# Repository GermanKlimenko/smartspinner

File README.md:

# Умный спиннер для трейдера

Проект **Смартлаба**. Выбранные визуальные направления: [«Пульс рынка»](public/assets/smartlab/market-full.png) и [«Биржевой сигнал»](public/assets/smartlab/signals-full.png). [Галерея на сайте](https://germanklimenko.github.io/smartspinner/#smartlab).

Это концептуальные изображения с демонстрационными котировками, не фотографии работающего прототипа. Свечной вариант не выбран и на сайте не размещён.

[Сайт проекта](https://germanklimenko.github.io/smartspinner/) · [Фото реального POV-вентилятора](public/assets/reference-fan/README.md)

## Текущий этап: неподвижный стенд B0.1

Документация для опытной ручной сборки подготовлена. **На железе не проверено.**
Цель конечного устройства: четыре луча, Ø100 мм, по 20 верхних и 12 торцевых RGB. Это целевые параметры, не характеристики испытанного образца.

- [Полный пакет стенда ZIP](bench/SmartSpinner_B01_DIY_Package.zip)
- [Инструкция PDF](bench/v0.1/output/pdf/SmartSpinner_B01_Bench.pdf)
- [Список покупок](bench/v0.1/shopping.md)
- [Исходники, схема соединений и прошивка](bench/v0.1/)
- [Результаты программных проверок](bench/v0.1/build/verification.txt)
- [Аудит электроники от 29.09.2026](audits/2026-09-29-electronics/README.md)

B0.1: UNO R3, 6 драйверов SM16306SJ, 32 выводных RGB LED, 96 каналов. Неподвижный опыт без аккумулятора и мотора. Не закреплять стенд на купленном голографическом вентиляторе.

## Старые версии сняты

**STOP FABRICATION. Прежние электрические файлы v0.4/v0.5 нельзя использовать для изготовления и подключения аккумулятора.**

Удалены из текущего каталога устаревшие версии v0.1/v0.2, электрические пакеты v0.4/v0.5 и прежние материалы с завышенной оценкой готовности. Они восстановимы из истории Git. Аудит относится к историческому коммиту [1635129](https://github.com/GermanKlimenko/smartspinner/tree/1635129707aff4e6b09a5e4b1feb32eedf14c7ca), поэтому его пути и контрольные суммы описывают именно тот снимок.

Сохранена параметрическая геометрия v0.3 как основа для переработки, а не согласованная с электроникой сборка. Визуализации — концептуальные рендеры, не фотографии работающего прототипа.

## Следующие шаги

1. Купить компоненты по списку B0.1 и собрать неподвижный стенд.
2. Проверить адресацию, токи, отключение, нагрев и оптические импульсы; заполнить протокол.
3. По результатам разработать новую компактную схему и PCB, согласовать с корпусом.
4. После ERC/DRC, DFM и проверки питания подготовить заказ 10 PCBA.

## Локальный запуск сайта

Node.js >= 22.13, pnpm. Команды: `pnpm install --frozen-lockfile`, `pnpm dev`, `pnpm build`.
Публикация — GitHub Pages через workflow в `.github/workflows/pages.yml`.

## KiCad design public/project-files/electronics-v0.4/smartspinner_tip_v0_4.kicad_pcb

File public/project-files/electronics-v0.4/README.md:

# Smart Spinner electronics v0.4 - Engineering Release Candidate

This package substantially closes the documentation gap of mechanical v0.3: it defines the electrical architecture, component selection, two KiCad PCB candidates with fully routed pixel chains, Gerbers, drill files, BOM, CPL/position data, assembly drawings, schematic PDF, power budget and bring-up plan.

## Board set

- Main board: four-layer, 1.0 mm, approximately 96 x 96 mm, 23.2 mm center hole, four M2 NPTH holes.
- Four identical tip boards: two-layer, 0.6 mm, 7.0 x 13.6 mm.
- Pixels: 80 top SK6805-EC15 plus 48 tip SK6805-EC10, split into eight independent chains (4 x 20 top and 4 x 12 tip).
- Controller: Raytac MDBT50Q-1MV2 (nRF52840); Hall index and BMI270 IMU.
- Power: protected 1S LiPo, 3.3 V logic LDO, switched TPS61023 5 V LED rail.

## Release status

This is an **engineering package for quotation and layout completion**, not yet a release for fabrication. The board geometry and pixel-chain routing are real and machine-readable, but the central power/control fan-out still has open connections. KiCad's generated DRC reports are included as the source of truth. No physical prototype has yet verified RF performance, Hall phase jitter, LED footprint orientation, thermal margin, battery current or balance.

Current generated DRC state (do not waive): main board has no track shorts after generation but retains open central/interface connections; the tip board retains four open interface fan-outs. Cosmetic silkscreen warnings are also present. The exact counts are recorded in `smartspinner_main_v0_4_drc.txt`, `smartspinner_tip_v0_4_drc.txt` and `smartspinner_v0_4_release_status.json`.

Before fabrication the assembler must:

1. Close every unconnected item in both DRC reports; rerun DRC with zero copper errors before plotting fabrication Gerbers.
2. Map every custom embedded footprint to the exact MPN land pattern and confirm pin-1 orientation.
3. Review the Raytac antenna keep-out on all copper/paste/mask layers and request an RF DFM check.
4. Complete/verify the boost passive network and all decoupling against component datasheets.
5. Confirm 4-layer stackup, 1.0 mm main board and 0.6 mm tip boards; panelize tip boards.
6. Build one first article, test it in a guarded fixture, then authorize the remaining nine.

## Files

- `smartspinner_main_v0_4.kicad_pcb`, `smartspinner_tip_v0_4.kicad_pcb` - editable PCB sources.
- `gerber/` - review-only copper, mask, silkscreen, edge cuts and Excellon drill outputs; regenerate after zero-error DRC.
- `assembly/*.csv` - KiCad position files (CPL source).
- `smartspinner_v0_4_bom.csv` - purchasing BOM with exact preferred MPNs and sourcing identifiers.
- `smartspinner_v0_4_netlist.csv` - interface/net summary.
- `smartspinner_v0_4_schematic.pdf` - four-page electrical design specification.
- `smartspinner_v0_4_fabrication_drawing.pdf` - dimensions, stackup and acceptance notes.
- `smartspinner_v0_4_power_budget.json` - preliminary energy model.
- `smartspinner_v0_4_bringup.md` - first-article test and safety procedure.

## Safety

Use only protected matched cells with welded tabs, physically retained by the enclosure. Do not charge while spinning. First spin tests must use a polycarbonate guard, remote drive and staged RPM limits. A complete loss-of-part containment test is required before handheld demonstrations.

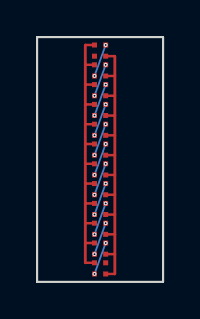
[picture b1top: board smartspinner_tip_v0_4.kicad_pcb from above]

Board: 2 copper layers, 7.0 x 13.6 mm, 13 parts (1 on the bottom side), 15 nets.

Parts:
J1: MAIN_BOARD_SOLDER_4; SmartSpinner_MAIN_BOARD_SOLDER_4
TD1, TD2, TD3, TD4, TD5, TD6, TD7, TD8, TD9, TD10, TD11, TD12: SK6805-EC10; SmartSpinner_SK6805-EC10

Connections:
+5V_LED: J1.1, TD1.1, TD2.1, TD3.1, TD4.1, TD5.1, TD6.1, TD7.1, TD8.1, TD9.1, TD10.1, TD11.1, TD12.1
DIN: J1.3, TD1.4
DOUT: J1.4, TD12.2
GND: J1.2, TD1.3, TD2.3, TD3.3, TD4.3, TD5.3, TD6.3, TD7.3, TD8.3, TD9.3, TD10.3, TD11.3, TD12.3
PIX_01: TD1.2, TD2.4
PIX_02: TD2.2, TD3.4
PIX_03: TD3.2, TD4.4
PIX_04: TD4.2, TD5.4
PIX_05: TD5.2, TD6.4
PIX_06: TD6.2, TD7.4
PIX_07: TD7.2, TD8.4
PIX_08: TD8.2, TD9.4
PIX_09: TD9.2, TD10.4
PIX_10: TD10.2, TD11.4
PIX_11: TD11.2, TD12.4

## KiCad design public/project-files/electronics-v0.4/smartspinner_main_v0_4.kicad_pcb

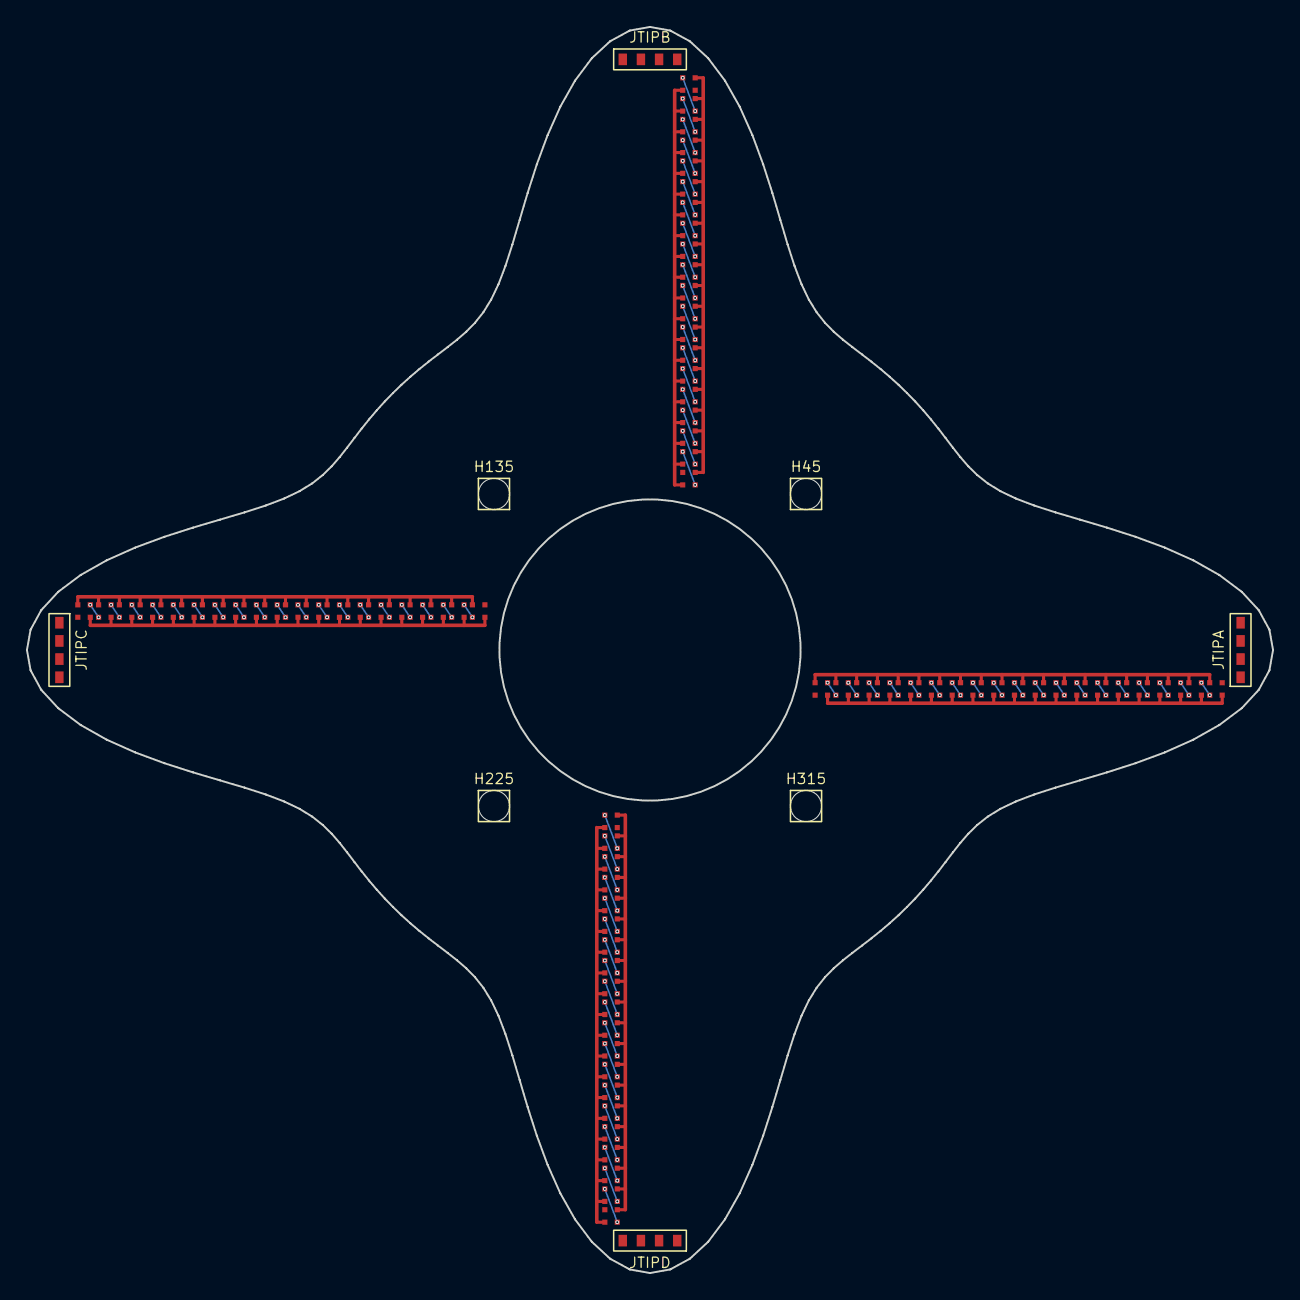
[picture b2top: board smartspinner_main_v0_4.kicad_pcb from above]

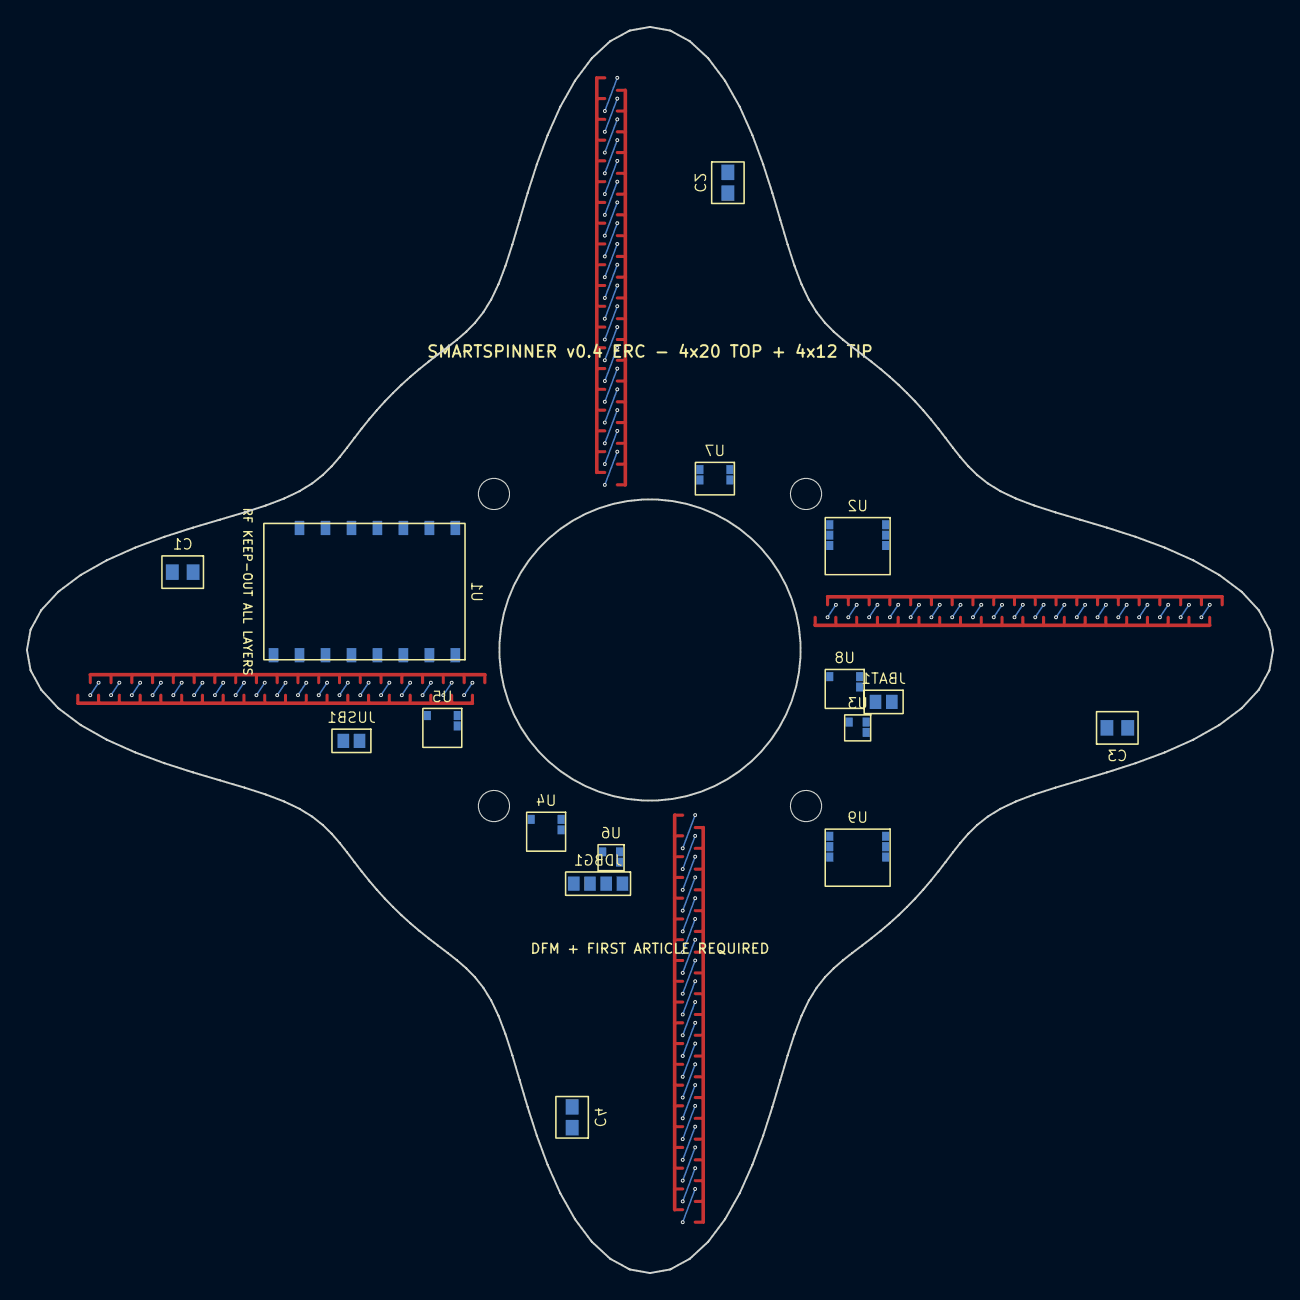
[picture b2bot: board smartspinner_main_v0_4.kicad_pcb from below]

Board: 4 copper layers, 96.0 x 96.0 mm, 104 parts (16 on the bottom side), 94 nets.

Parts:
C1, C2, C3, C4: 100uF_6V3_1210; SmartSpinner_100uF_6V3_1210
D1, D2, D3, D4, D5, D6, D7, D8, D9, D10, D11, D12, D13, D14, D15, D16, D17, D18, D19, D20, D21, D22, D23, D24, D25, D26, D27, D28, D29, D30, D31, D32, D33, D34, D35, D36, D37, D38, D39, D40, D41, D42, D43, D44, D45, D46, D47, D48, D49, D50, D51, D52, D53, D54, D55, D56, D57, D58, D59, D60, D61, D62, D63, D64, D65, D66, D67, D68, D69, D70, D71, D72, D73, D74, D75, D76, D77, D78, D79, D80: SK6805-EC15; SmartSpinner_SK6805-EC15
H45, H135, H225, H315: M2_NPTH; SmartSpinner_M2_NPTH
JBAT1: BATTERY_PADS; SmartSpinner_BATTERY_PADS
JDBG1: SWD_PADS; SmartSpinner_SWD_PADS
JTIPA: TIP_BOARD_SOLDER_4; SmartSpinner_TIP_BOARD_SOLDER_4
JTIPB: TIP_BOARD_SOLDER_4; SmartSpinner_TIP_BOARD_SOLDER_4
JTIPC: TIP_BOARD_SOLDER_4; SmartSpinner_TIP_BOARD_SOLDER_4
JTIPD: TIP_BOARD_SOLDER_4; SmartSpinner_TIP_BOARD_SOLDER_4
JUSB1: USB_CHARGE_PADS; SmartSpinner_USB_CHARGE_PADS
U1: MDBT50Q-1MV2; SmartSpinner_MDBT50Q-1MV2
U2: 74AHCT125PW_TOP; SmartSpinner_74AHCT125PW_TOP
U3: TPS61023DRL; SmartSpinner_TPS61023DRL
U4: TPS7A2033PDBV; SmartSpinner_TPS7A2033PDBV
U5: MCP73831-2ACI_OT; SmartSpinner_MCP73831-2ACI_OT
U6: DRV5033AJQLPGM; SmartSpinner_DRV5033AJQLPGM
U7: BMI270; SmartSpinner_BMI270
U8: TPS22918DBVR; SmartSpinner_TPS22918DBVR
U9: 74AHCT125PW_TIP; SmartSpinner_74AHCT125PW_TIP

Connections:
+3V3: JDBG1.1, U1.2, U2.1, U4.3, U6.1, U7.1, U9.1
+5V_LED: C1.1, C2.1, C3.1, C4.1, D1.1, D2.1, D3.1, D4.1, D5.1, D6.1, D7.1, D8.1, D9.1, D10.1, D11.1, D12.1, D13.1, D14.1, D15.1, D16.1, D17.1, D18.1, D19.1, D20.1, D21.1, D22.1, D23.1, D24.1, D25.1, D26.1, D27.1, D28.1, D29.1, D30.1, D31.1, D32.1, D33.1, D34.1, D35.1, D36.1, D37.1, D38.1, D39.1, D40.1, D41.1, D42.1, D43.1, D44.1, D45.1, D46.1, D47.1, D48.1, D49.1, D50.1, D51.1, D52.1, D53.1, D54.1, D55.1, D56.1, D57.1, D58.1, D59.1, D60.1, D61.1, D62.1, D63.1, D64.1, D65.1, D66.1, D67.1, D68.1, D69.1, D70.1, D71.1, D72.1, D73.1, D74.1, D75.1, D76.1, D77.1, D78.1, D79.1, D80.1, JTIPA.1, JTIPB.1, JTIPC.1, JTIPD.1, U3.3, U8.3
GND: C1.2, C2.2, C3.2, C4.2, D1.3, D2.3, D3.3, D4.3, D5.3, D6.3, D7.3, D8.3, D9.3, D10.3, D11.3, D12.3, D13.3, D14.3, D15.3, D16.3, D17.3, D18.3, D19.3, D20.3, D21.3, D22.3, D23.3, D24.3, D25.3, D26.3, D27.3, D28.3, D29.3, D30.3, D31.3, D32.3, D33.3, D34.3, D35.3, D36.3, D37.3, D38.3, D39.3, D40.3, D41.3, D42.3, D43.3, D44.3, D45.3, D46.3, D47.3, D48.3, D49.3, D50.3, D51.3, D52.3, D53.3, D54.3, D55.3, D56.3, D57.3, D58.3, D59.3, D60.3, D61.3, D62.3, D63.3, D64.3, D65.3, D66.3, D67.3, D68.3, D69.3, D70.3, D71.3, D72.3, D73.3, D74.3, D75.3, D76.3, D77.3, D78.3, D79.3, D80.3, JBAT1.2, JDBG1.2, JTIPA.2, JTIPB.2, JTIPC.2, JTIPD.2, JUSB1.2, U1.1, U2.2, U3.2, U4.2, U5.2, U6.2, U7.2, U8.2, U9.2
HALL: U1.11, U6.3
LED_A_01: D1.2, D2.4
LED_A_02: D2.2, D3.4
LED_A_03: D3.2, D4.4
LED_A_04: D4.2, D5.4
LED_A_05: D5.2, D6.4
LED_A_06: D6.2, D7.4
LED_A_07: D7.2, D8.4
LED_A_08: D8.2, D9.4
LED_A_09: D9.2, D10.4
LED_A_10: D10.2, D11.4
LED_A_11: D11.2, D12.4
LED_A_12: D12.2, D13.4
LED_A_13: D13.2, D14.4
LED_A_14: D14.2, D15.4
LED_A_15: D15.2, D16.4
LED_A_16: D16.2, D17.4
LED_A_17: D17.2, D18.4
LED_A_18: D18.2, D19.4
LED_A_19: D19.2, D20.4
LED_B_01: D21.2, D22.4
LED_B_02: D22.2, D23.4
LED_B_03: D23.2, D24.4
LED_B_04: D24.2, D25.4
LED_B_05: D25.2, D26.4
LED_B_06: D26.2, D27.4
LED_B_07: D27.2, D28.4
LED_B_08: D28.2, D29.4
LED_B_09: D29.2, D30.4
LED_B_10: D30.2, D31.4
LED_B_11: D31.2, D32.4
LED_B_12: D32.2, D33.4
LED_B_13: D33.2, D34.4
LED_B_14: D34.2, D35.4
LED_B_15: D35.2, D36.4
LED_B_16: D36.2, D37.4
LED_B_17: D37.2, D38.4
LED_B_18: D38.2, D39.4
LED_B_19: D39.2, D40.4
LED_C_01: D41.2, D42.4
LED_C_02: D42.2, D43.4
LED_C_03: D43.2, D44.4
LED_C_04: D44.2, D45.4
LED_C_05: D45.2, D46.4
LED_C_06: D46.2, D47.4
LED_C_07: D47.2, D48.4
LED_C_08: D48.2, D49.4
LED_C_09: D49.2, D50.4
LED_C_10: D50.2, D51.4
LED_C_11: D51.2, D52.4
LED_C_12: D52.2, D53.4
LED_C_13: D53.2, D54.4
LED_C_14: D54.2, D55.4
LED_C_15: D55.2, D56.4
LED_C_16: D56.2, D57.4
LED_C_17: D57.2, D58.4
LED_C_18: D58.2, D59.4
LED_C_19: D59.2, D60.4
LED_D_01: D61.2, D62.4
LED_D_02: D62.2, D63.4
LED_D_03: D63.2, D64.4
LED_D_04: D64.2, D65.4
LED_D_05: D65.2, D66.4
LED_D_06: D66.2, D67.4
LED_D_07: D67.2, D68.4
LED_D_08: D68.2, D69.4
LED_D_09: D69.2, D70.4
LED_D_10: D70.2, D71.4
LED_D_11: D71.2, D72.4
LED_D_12: D72.2, D73.4
LED_D_13: D73.2, D74.4
LED_D_14: D74.2, D75.4
LED_D_15: D75.2, D76.4
LED_D_16: D76.2, D77.4
LED_D_17: D77.2, D78.4
LED_D_18: D78.2, D79.4
LED_D_19: D79.2, D80.4
SCL: U1.13, U7.4
SDA: U1.12, U7.3
SWCLK: JDBG1.4, U1.15
SWDIO: JDBG1.3, U1.14
TIP_A_DIN: JTIPA.3, U1.7, U9.3
TIP_B_DIN: JTIPB.3, U1.8, U9.4
TIP_C_DIN: JTIPC.3, U1.9, U9.5
TIP_D_DIN: JTIPD.3, U1.10, U9.6
TOP_A_DIN: D1.4, U1.3, U2.3
TOP_B_DIN: D21.4, U1.4, U2.4
TOP_C_DIN: D41.4, U1.5, U2.5
TOP_D_DIN: D61.4, U1.6, U2.6
USB_5V: JUSB1.1, U5.1
VBAT: JBAT1.1, U3.1, U4.1, U5.3, U8.1

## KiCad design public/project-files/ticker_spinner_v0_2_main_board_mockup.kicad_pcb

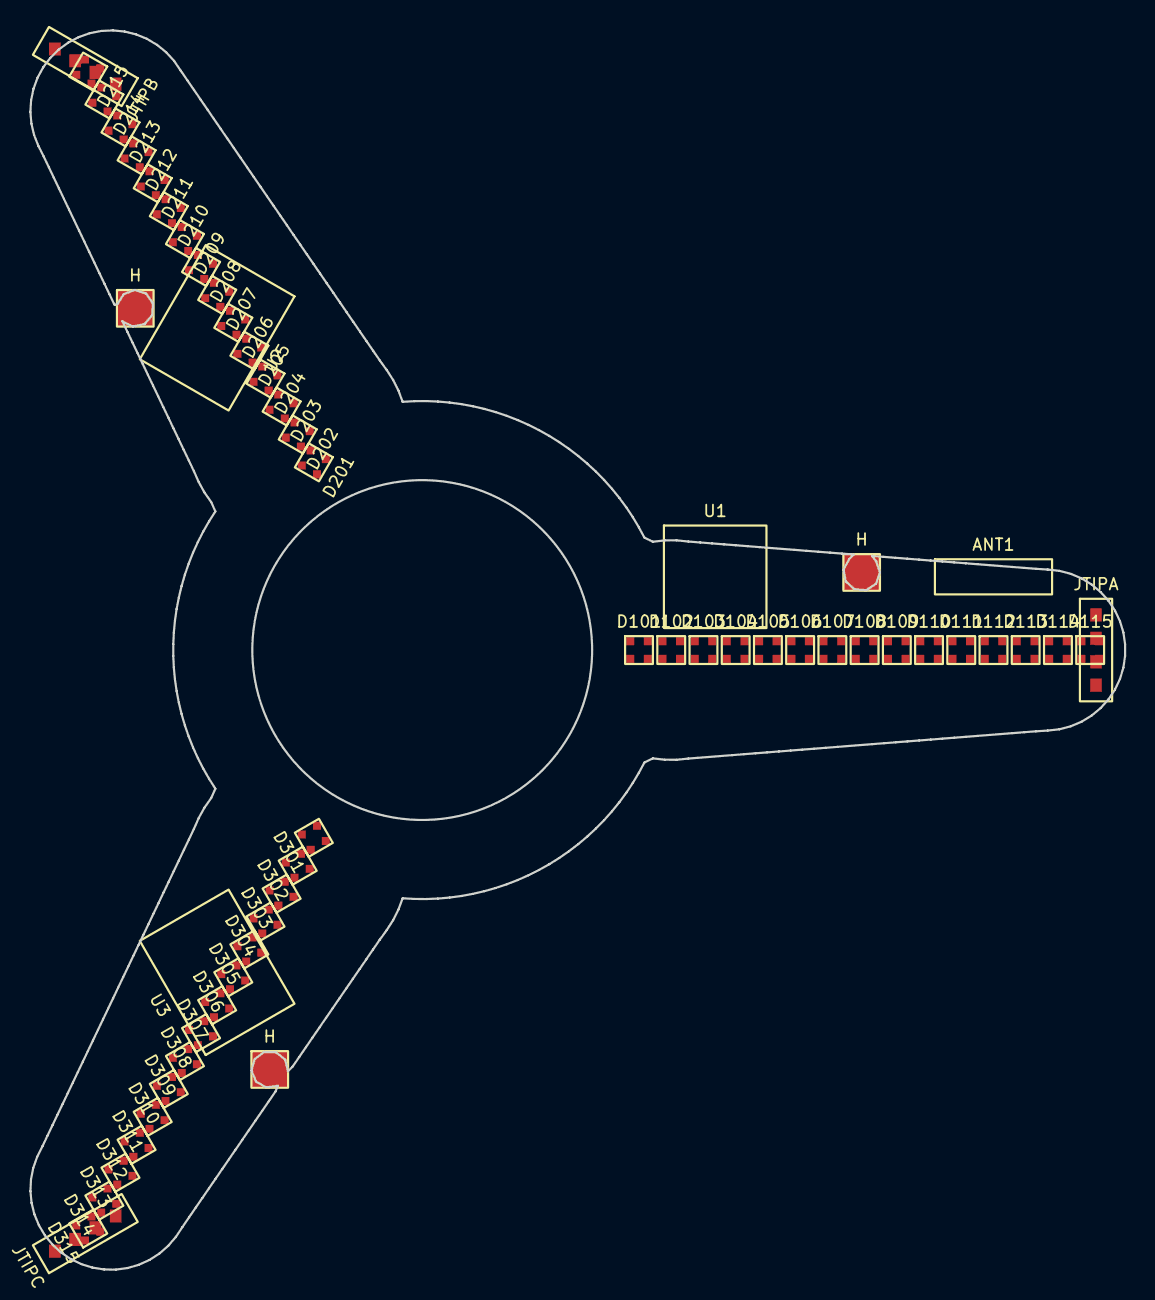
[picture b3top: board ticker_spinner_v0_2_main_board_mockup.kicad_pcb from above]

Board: 2 copper layers, 74.7 x 84.6 mm, 55 parts (0 on the bottom side), 47 nets, no tracks yet.

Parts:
ANT1: BLE_ANTENNA_KEEP_OUT
D101, D102, D103, D104, D105, D106, D107, D108, D109, D110, D111, D112, D113, D114, D115, D201, D202, D203, D204, D205, D206, D207, D208, D209, D210, D211, D212, D213, D214, D215, D301, D302, D303, D304, D305, D306, D307, D308, D309, D310, D311, D312, D313, D314, D315: RGB_2020_ADDR
H: M2_NPTH
H#2, H#3: M2_NPTH
JTIPA: TIP_BOARD_4PAD
JTIPB: TIP_BOARD_4PAD
JTIPC: TIP_BOARD_4PAD
U1: NRF52840_QFN_WLCSP_TBD
U2: LIPO_CHARGER_PROTECT_TBD
U3: BOOST_5V_1P5A_TBD

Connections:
+5V: D101.1, D102.1, D103.1, D104.1, D105.1, D106.1, D107.1, D108.1, D109.1, D110.1, D111.1, D112.1, D113.1, D114.1, D115.1, D201.1, D202.1, D203.1, D204.1, D205.1, D206.1, D207.1, D208.1, D209.1, D210.1, D211.1, D212.1, D213.1, D214.1, D215.1, D301.1, D302.1, D303.1, D304.1, D305.1, D306.1, D307.1, D308.1, D309.1, D310.1, D311.1, D312.1, D313.1, D314.1, D315.1, JTIPA.1, JTIPB.1, JTIPC.1
GND: D101.3, D102.3, D103.3, D104.3, D105.3, D106.3, D107.3, D108.3, D109.3, D110.3, D111.3, D112.3, D113.3, D114.3, D115.3, D201.3, D202.3, D203.3, D204.3, D205.3, D206.3, D207.3, D208.3, D209.3, D210.3, D211.3, D212.3, D213.3, D214.3, D215.3, D301.3, D302.3, D303.3, D304.3, D305.3, D306.3, D307.3, D308.3, D309.3, D310.3, D311.3, D312.3, D313.3, D314.3, D315.3, JTIPA.2, JTIPB.2, JTIPC.2
TOP_A_01: D101.2, D102.4
TOP_A_02: D102.2, D103.4
TOP_A_03: D103.2, D104.4
TOP_A_04: D104.2, D105.4
TOP_A_05: D105.2, D106.4
TOP_A_06: D106.2, D107.4
TOP_A_07: D107.2, D108.4
TOP_A_08: D108.2, D109.4
TOP_A_09: D109.2, D110.4
TOP_A_10: D110.2, D111.4
TOP_A_11: D111.2, D112.4
TOP_A_12: D112.2, D113.4
TOP_A_13: D113.2, D114.4
TOP_A_14: D114.2, D115.4
TOP_A_15: D115.2, JTIPA.3
TOP_B_01: D201.2, D202.4
TOP_B_02: D202.2, D203.4
TOP_B_03: D203.2, D204.4
TOP_B_04: D204.2, D205.4
TOP_B_05: D205.2, D206.4
TOP_B_06: D206.2, D207.4
TOP_B_07: D207.2, D208.4
TOP_B_08: D208.2, D209.4
TOP_B_09: D209.2, D210.4
TOP_B_10: D210.2, D211.4
TOP_B_11: D211.2, D212.4
TOP_B_12: D212.2, D213.4
TOP_B_13: D213.2, D214.4
TOP_B_14: D214.2, D215.4
TOP_B_15: D215.2, JTIPB.3
TOP_C_01: D301.2, D302.4
TOP_C_02: D302.2, D303.4
TOP_C_03: D303.2, D304.4
TOP_C_04: D304.2, D305.4
TOP_C_05: D305.2, D306.4
TOP_C_06: D306.2, D307.4
TOP_C_07: D307.2, D308.4
TOP_C_08: D308.2, D309.4
TOP_C_09: D309.2, D310.4
TOP_C_10: D310.2, D311.4
TOP_C_11: D311.2, D312.4
TOP_C_12: D312.2, D313.4
TOP_C_13: D313.2, D314.4
TOP_C_14: D314.2, D315.4
TOP_C_15: D315.2, JTIPC.3

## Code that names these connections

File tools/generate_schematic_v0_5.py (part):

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    ], 133, 145, width=19)

    place(s, "U6", "DRV5033AJQLPGM", [Pin("1", "VCC", "3V3", "L"), Pin("2", "GND", "GND", "L"), Pin("3", "OUT", "HALL_INT", "R")], 135, 175, width=22, footprint="Package_TO_SOT_SMD:SOT-23", datasheet="https://www.ti.com/lit/ds/symlink/drv5033.pdf")
    place(s, *two_pin("R6", "10k HALL PULLUP", "HALL_INT", "3V3"), 175, 174, width=18)
    place(s, "U7", "BMI270", [
        Pin("5", "VDDIO", "3V3", "L"), Pin("8", "VDD", "3V3", "L"), Pin("6", "GNDIO", "GND", "L"), Pin("7", "GND", "GND", "L"),
        Pin("12", "CSB", "3V3", "L"), Pin("1", "SDO/SA0", "GND", "L"), Pin("14", "SDX/SDA", "SDA", "R"), Pin("13", "SCX/SCL", "SCL", "R"),
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        chains.append((f"D{1+i*20}-D{20+i*20}", f"20x SK6805-EC15 TOP {ch}", f"TOP_{ch}_5V", 225 + (i % 2) * 62, 230 + (i // 2) * 30))
        chains.append((f"TD{1+i*12}-TD{12+i*12}", f"12x SK6805-EC10 TIP {ch}", f"TIP_{ch}_5V", 225 + (i % 2) * 62, 288 + (i // 2) * 30))
    for ref, value, din, x, y in chains:
        place(s, ref, value, [Pin("1", "DIN", din, "L"), Pin("2", "VDD", "+5V_LED", "L"), Pin("3", "GND", "GND", "L"), Pin("4", "DOUT", None, "R")], x, y, width=31)

    note(s, "ENGINEERING REVIEW NOTES", 28, 330, 0, 0, title=True)
    note(s,
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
